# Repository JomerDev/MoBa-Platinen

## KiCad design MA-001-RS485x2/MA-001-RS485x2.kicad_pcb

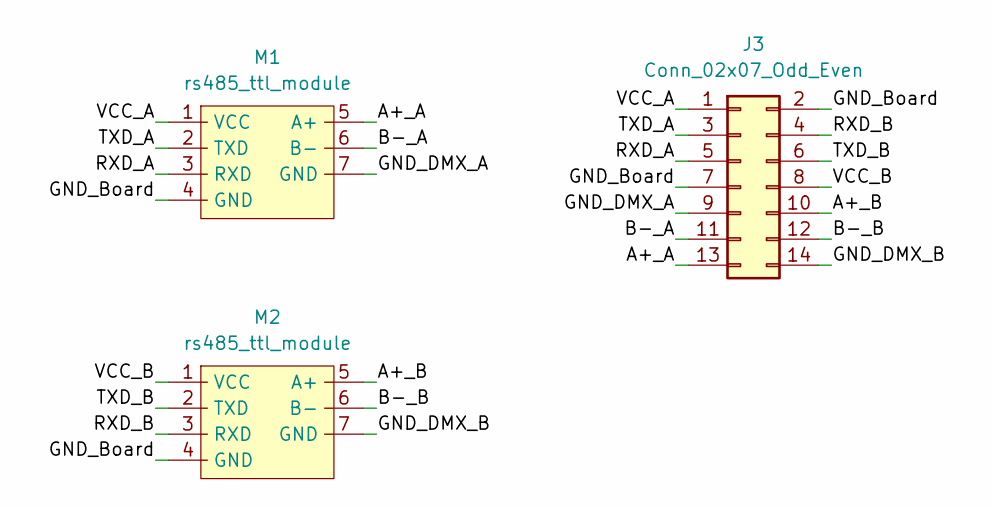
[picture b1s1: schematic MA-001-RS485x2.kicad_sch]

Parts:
J3: Conn_02x07_Odd_Even; 2x7_Pins_Vertical_PCB_Edge
M1, M2: rs485_ttl_module

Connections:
/A+_A: J3.13, M1.5 (A+)
/A+_B: J3.10, M2.5 (A+)
/B-_A: J3.11, M1.6 (B-)
/B-_B: J3.12, M2.6 (B-)
/GND_Board: J3.2, J3.7, M1.4 (GND), M2.4 (GND)
/GND_DMX_A: J3.9, M1.7 (GND)
/GND_DMX_B: J3.14, M2.7 (GND)
/RXD_A: J3.5, M1.3 (RXD)
/RXD_B: J3.4, M2.3 (RXD)
/TXD_A: J3.3, M1.2 (TXD)
/TXD_B: J3.6, M2.2 (TXD)
/VCC_A: J3.1, M1.1 (VCC)
/VCC_B: J3.8, M2.1 (VCC)

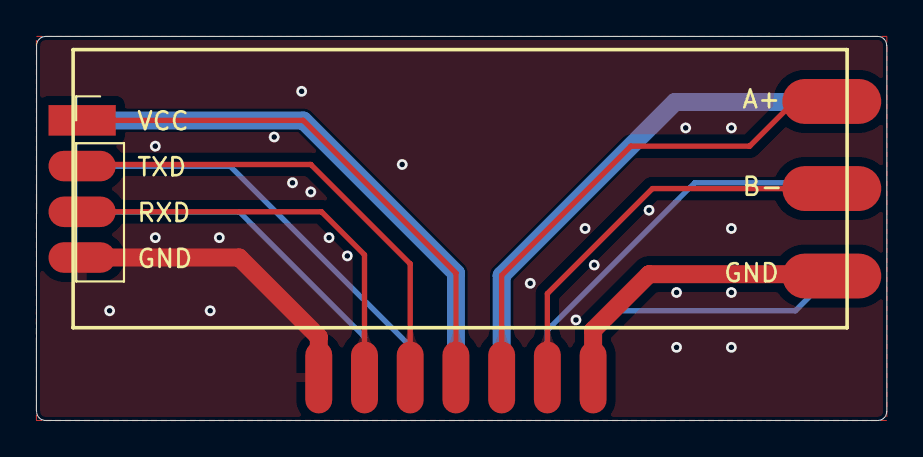
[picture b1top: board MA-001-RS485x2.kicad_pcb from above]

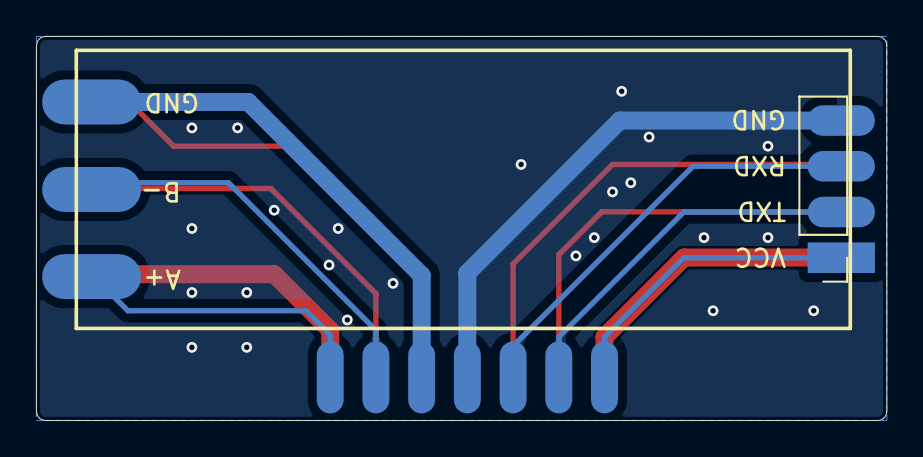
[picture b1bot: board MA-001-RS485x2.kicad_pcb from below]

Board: 2 copper layers, 47.2 x 21.3 mm, 3 parts (2 on the bottom side), 13 nets.

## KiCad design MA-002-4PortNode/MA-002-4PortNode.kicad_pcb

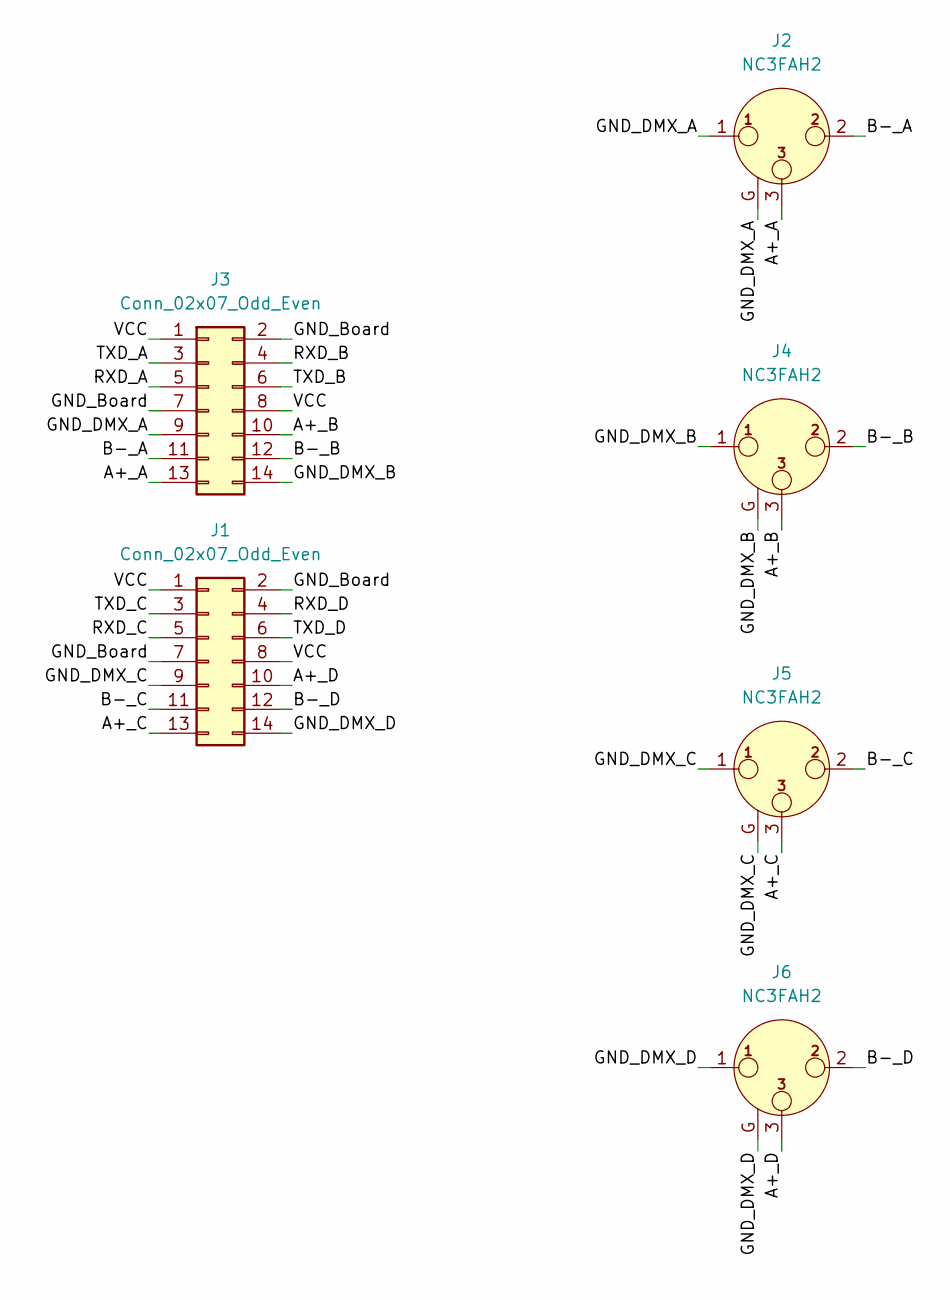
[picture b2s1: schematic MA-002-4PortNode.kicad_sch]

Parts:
J1, J3: Conn_02x07_Odd_Even; PinHeader_2x07_P2.54mm_Vertical
J2, J4, J5, J6: NC3FAH2; Jack_XLR_Neutrik_NC3MBH_Horizontal

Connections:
/A+_A: J2.3, J3.13
/A+_B: J3.10, J4.3
/A+_C: J1.13, J5.3
/A+_D: J1.10, J6.3
/B-_A: J2.2, J3.11
/B-_B: J3.12, J4.2
/B-_C: J1.11, J5.2
/B-_D: J1.12, J6.2
/GND_Board: J1.2, J1.7, J3.2, J3.7
/GND_DMX_A: J2.1, J2.G, J3.9
/GND_DMX_B: J3.14, J4.1, J4.G
/GND_DMX_C: J1.9, J5.1, J5.G
/GND_DMX_D: J1.14, J6.1, J6.G
/RXD_A: J3.5
/RXD_B: J3.4
/RXD_C: J1.5
/RXD_D: J1.4
/TXD_A: J3.3
/TXD_B: J3.6
/TXD_C: J1.3
/TXD_D: J1.6
/VCC: J1.1, J1.8, J3.1, J3.8

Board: 2 copper layers, 6 parts (0 on the bottom side), 14 nets, no tracks yet.

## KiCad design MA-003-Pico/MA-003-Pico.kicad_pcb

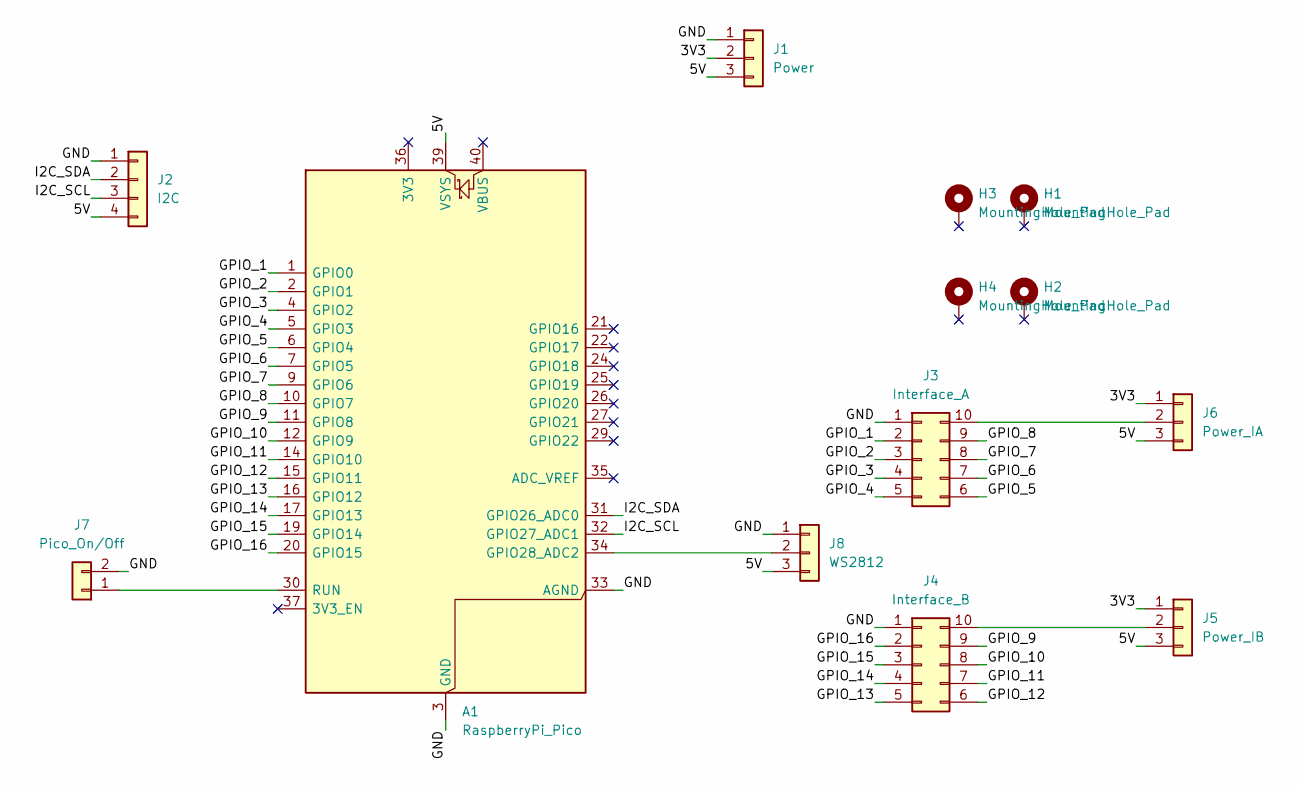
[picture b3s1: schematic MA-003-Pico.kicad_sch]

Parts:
A1: RaspberryPi_Pico; RaspberryPi_Pico_Common_SMD
H1, H2, H3, H4: MountingHole_Pad; MountingHole_2.7mm_M2.5_DIN965_Pad
J1: Power; Molex_KK-254_AE-6410-03A_1x03_P2.54mm_Vertical
J2: I2C; Molex_KK-254_AE-6410-04A_1x04_P2.54mm_Vertical
J3: Interface_A; IDC-Header_2x05_P2.54mm_Vertical
J4: Interface_B; IDC-Header_2x05_P2.54mm_Vertical
J5: Power_IB; PinHeader_1x03_P2.54mm_Vertical
J6: Power_IA; PinHeader_1x03_P2.54mm_Vertical
J7: Pico_On/Off; PinHeader_1x02_P2.54mm_Vertical
J8: WS2812; Molex_KK-254_AE-6410-03A_1x03_P2.54mm_Vertical

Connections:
/3V3: J1.2, J5.1, J6.1
/5V: A1.39 (VSYS), J1.3, J2.4, J5.3, J6.3, J8.3
/GND: A1.3 (GND), A1.8 (GND), A1.13 (GND), A1.18 (GND), A1.23 (GND), A1.28 (GND), A1.33 (AGND), A1.38 (GND), J1.1, J2.1, J3.1, J4.1, J7.2, J8.1
/GPIO_1: A1.1 (GPIO0), J3.2
/GPIO_2: A1.2 (GPIO1), J3.3
/GPIO_3: A1.4 (GPIO2), J3.4
/GPIO_4: A1.5 (GPIO3), J3.5
/GPIO_5: A1.6 (GPIO4), J3.6
/GPIO_6: A1.7 (GPIO5), J3.7
/GPIO_7: A1.9 (GPIO6), J3.8
/GPIO_8: A1.10 (GPIO7), J3.9
/GPIO_9: A1.11 (GPIO8), J4.9
/GPIO_10: A1.12 (GPIO9), J4.8
/GPIO_11: A1.14 (GPIO10), J4.7
/GPIO_12: A1.15 (GPIO11), J4.6
/GPIO_13: A1.16 (GPIO12), J4.5
/GPIO_14: A1.17 (GPIO13), J4.4
/GPIO_15: A1.19 (GPIO14), J4.3
/GPIO_16: A1.20 (GPIO15), J4.2
/I2C_SCL: A1.32 (GPIO27_ADC1), J2.3
/I2C_SDA: A1.31 (GPIO26_ADC0), J2.2
unnamed: A1.34 (GPIO28_ADC2), J8.2
unnamed: A1.30 (RUN), J7.1
unnamed: J3.10, J6.2
unnamed: J4.10, J5.2

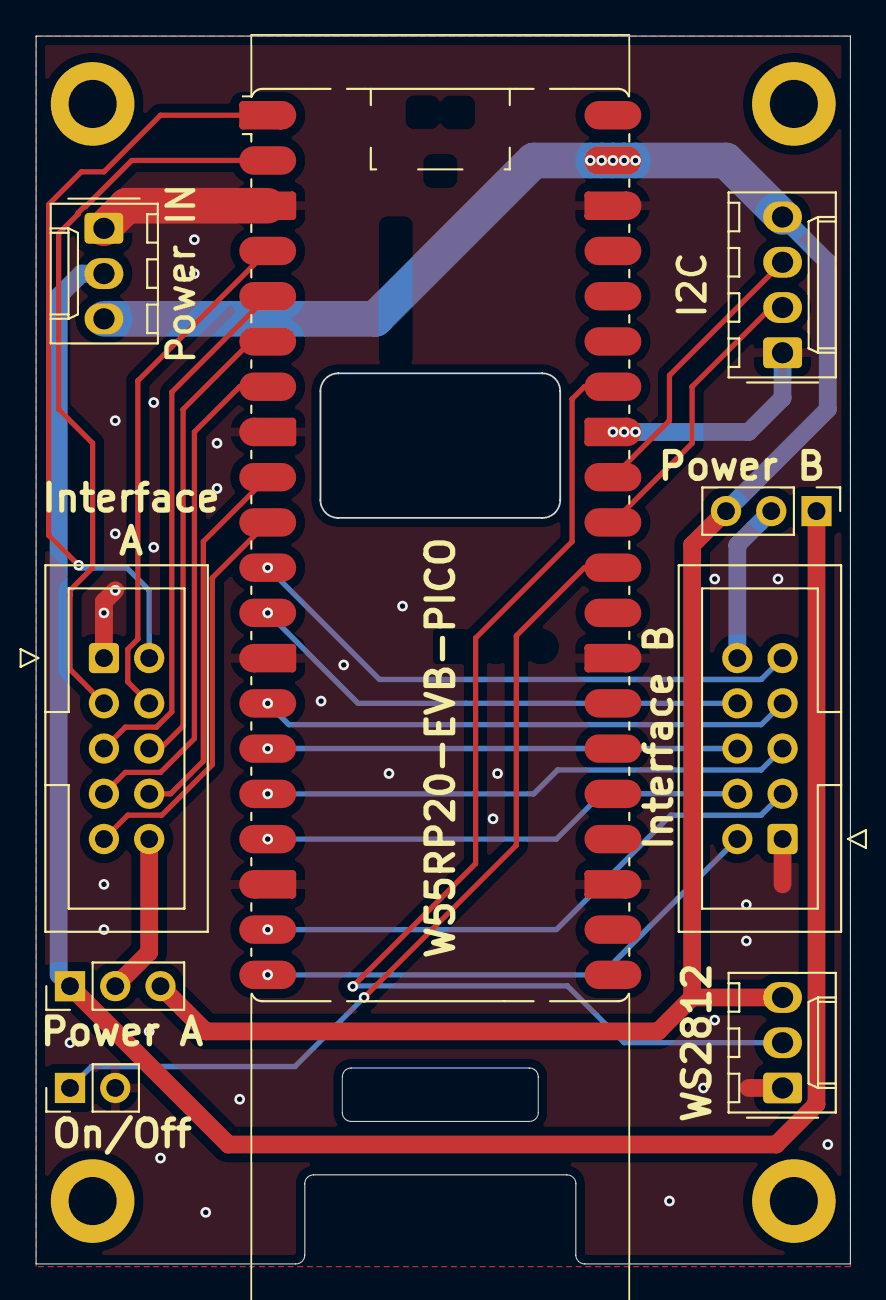
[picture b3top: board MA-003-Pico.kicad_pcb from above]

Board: 2 copper layers, 45.7 x 68.9 mm, 13 parts (0 on the bottom side), 25 nets.

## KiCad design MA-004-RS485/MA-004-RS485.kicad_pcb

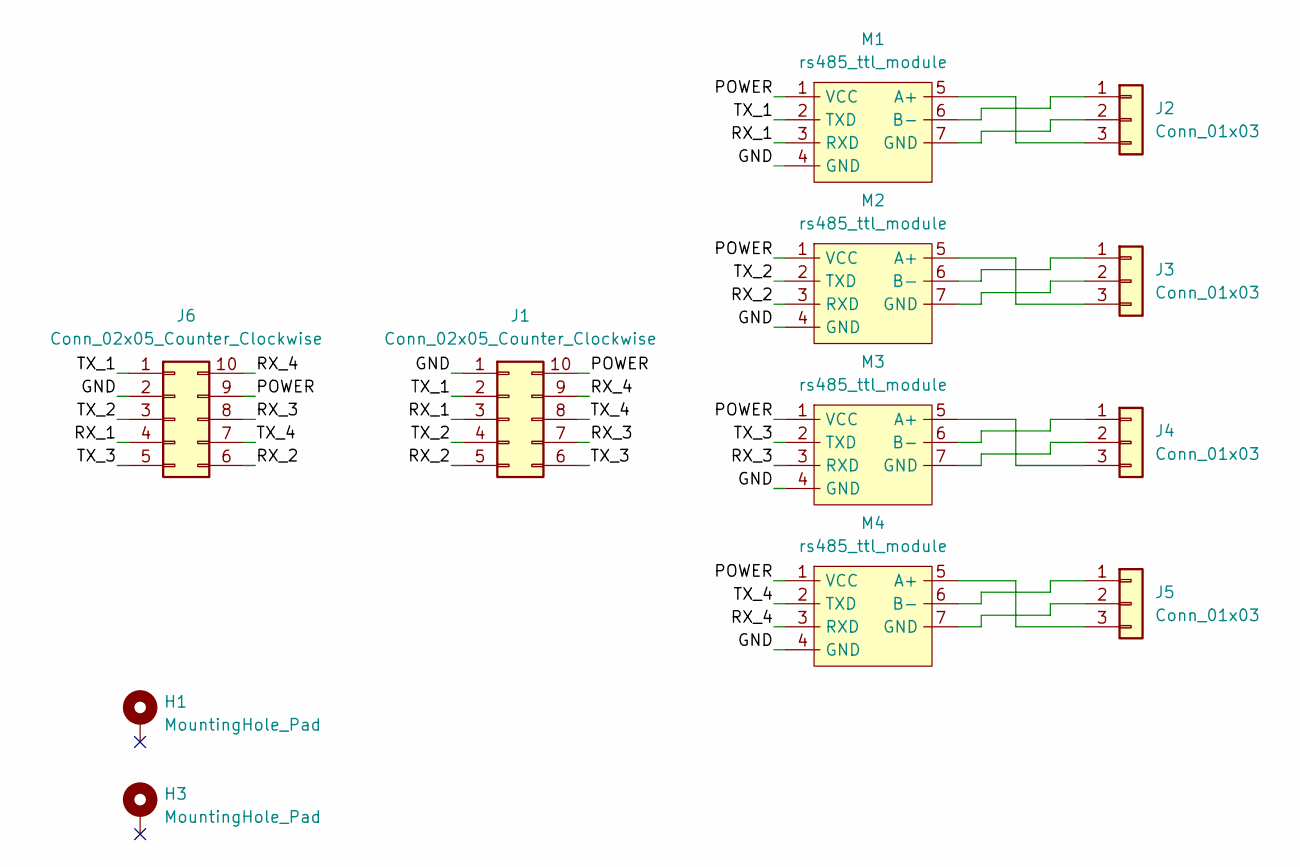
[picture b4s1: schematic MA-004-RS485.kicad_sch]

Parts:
H1, H3: MountingHole_Pad; MountingHole_2.7mm_M2.5_DIN965_Pad
J1: Conn_02x05_Counter_Clockwise; IDC-Header_2x05_P2.54mm_Vertical
J2, J3, J4, J5: Conn_01x03; Molex_KK-254_AE-6410-03A_1x03_P2.54mm_Vertical
J6: Conn_02x05_Counter_Clockwise; PinHeader_2x05_P2.54mm_Horizontal
M1, M2, M3, M4: rs485_ttl_module; rs485_ttl_module_short

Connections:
/GND: J1.1, J6.2, M1.4 (GND), M2.4 (GND), M3.4 (GND), M4.4 (GND)
/POWER: J1.10, J6.9, M1.1 (VCC), M2.1 (VCC), M3.1 (VCC), M4.1 (VCC)
/RX_1: J1.3, J6.4, M1.3 (RXD)
/RX_2: J1.5, J6.6, M2.3 (RXD)
/RX_3: J1.7, J6.8, M3.3 (RXD)
/RX_4: J1.9, J6.10, M4.3 (RXD)
/TX_1: J1.2, J6.1, M1.2 (TXD)
/TX_2: J1.4, J6.3, M2.2 (TXD)
/TX_3: J1.6, J6.5, M3.2 (TXD)
/TX_4: J1.8, J6.7, M4.2 (TXD)
unnamed: J2.1, M1.6 (B-)
unnamed: J2.2, M1.7 (GND)
unnamed: J2.3, M1.5 (A+)
unnamed: J3.1, M2.6 (B-)
unnamed: J3.2, M2.7 (GND)
unnamed: J3.3, M2.5 (A+)
unnamed: J4.1, M3.6 (B-)
unnamed: J4.2, M3.7 (GND)
unnamed: J4.3, M3.5 (A+)
unnamed: J5.1, M4.6 (B-)
unnamed: J5.2, M4.7 (GND)
unnamed: J5.3, M4.5 (A+)

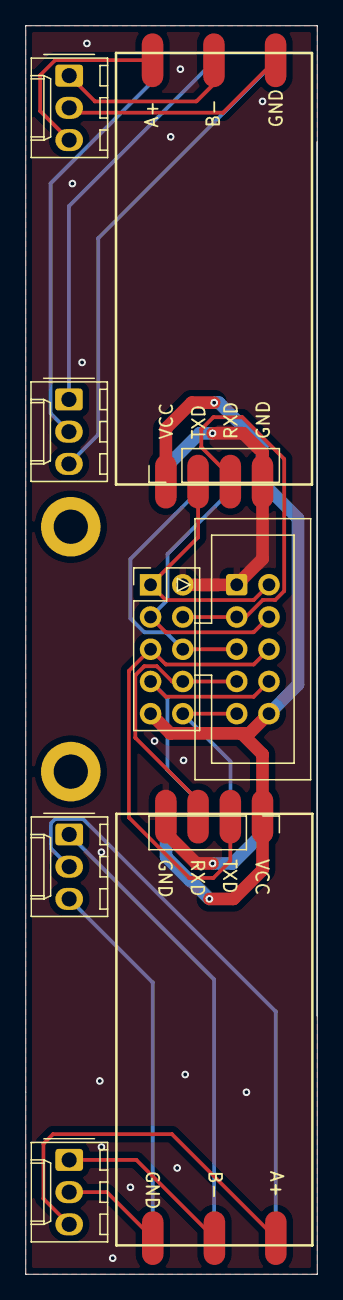
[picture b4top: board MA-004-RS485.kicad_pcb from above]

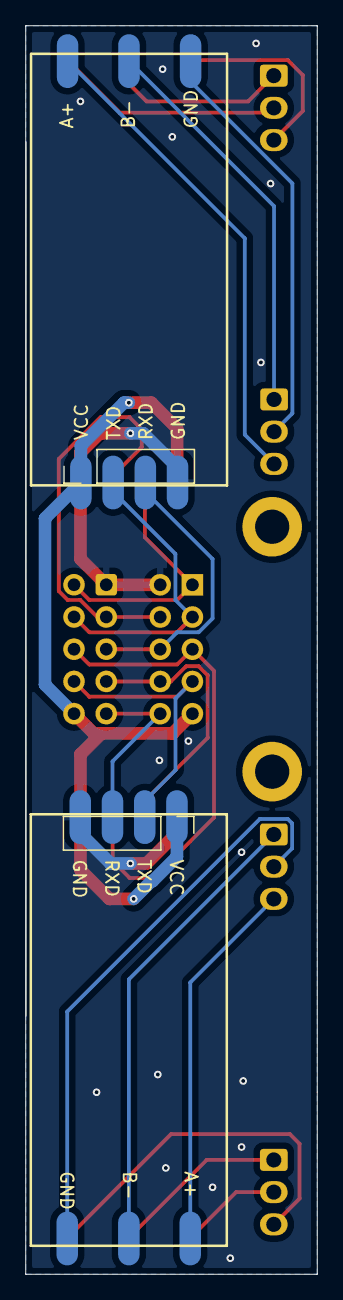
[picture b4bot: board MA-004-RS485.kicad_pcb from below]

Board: 2 copper layers, 23.0 x 98.4 mm, 12 parts (2 on the bottom side), 22 nets.

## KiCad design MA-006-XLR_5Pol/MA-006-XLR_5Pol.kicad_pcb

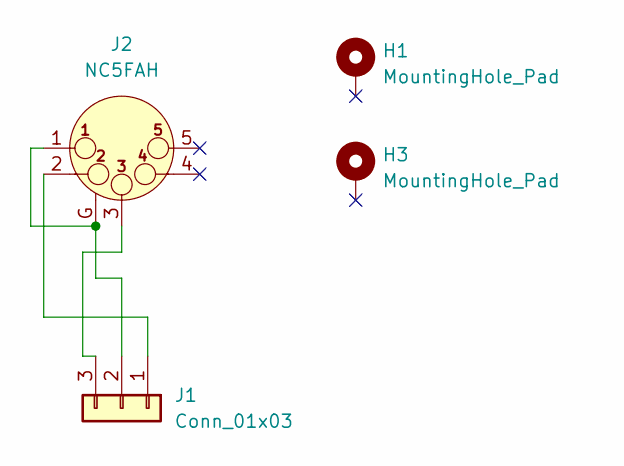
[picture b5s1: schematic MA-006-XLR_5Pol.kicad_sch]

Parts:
H1, H3: MountingHole_Pad; MountingHole_2.7mm_M2.5_DIN965_Pad
J1: Conn_01x03; Molex_KK-254_AE-6410-03A_1x03_P2.54mm_Vertical
J2: NC5FAH; Jack_XLR_Neutrik_NC5FAH_Horizontal

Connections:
unnamed: J1.1, J2.2
unnamed: J1.2, J2.1, J2.G
unnamed: J1.3, J2.3

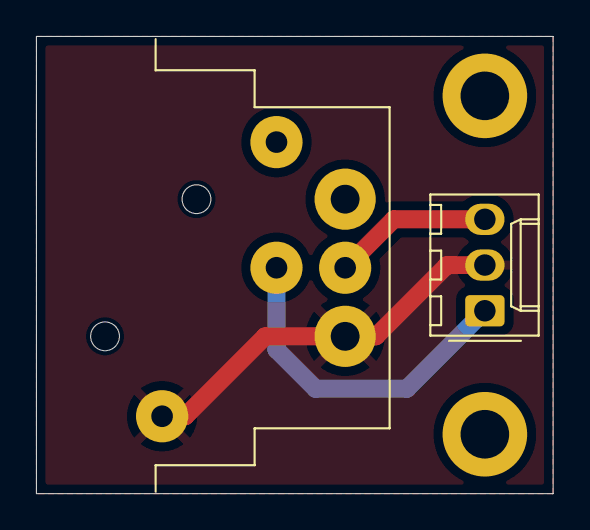
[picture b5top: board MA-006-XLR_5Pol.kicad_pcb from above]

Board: 2 copper layers, 28.7 x 25.4 mm, 4 parts (0 on the bottom side), 3 nets.
